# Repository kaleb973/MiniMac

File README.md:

# MiniMac
Presenting Mini Mac.   This is an external keypad to serve as functions that my current keyboard uses function keys for, like screenshot, which is (fn + u).   This project will serve as a huge productivity upgrade.

## Features
-128x32 OLED Display
-16 Keyswitches

## Note

I am also requesting a grant for a soldering iron (obviously with solder) for this project from Hack Club.

## Cad Model

I used heatset inserts and M3x16mm screws for the case. 

It has a simple Top and Bottom. The PCB sits in the middle.

This image displays the full model with the PCB inside.

Made in Fusion360.

## PCB

My PCB was made in KiCad

Schematic

PCB

## Firmware

This HackPad uses [QMK](https://qmk.fm/) firmware.

I intend to change the keys occasionally.

## BOM

Bill of Materials:

| Item | Description | Quantity |
| :--- | :--- | :--- |
| Cherry MX Switches | Keyswitches | 16 |
| DSA Keycaps | Keycaps | 16 |
| Heatset Inserts | Fasteners | 4 |
| M3x16mm Screws | Screws | 4 |
| 1N4148 Diodes | Through-Hole Diodes | 16 |
| 0.91-inch OLED Display | 128x32 Display | 1 |
| Seeed XIAO RP2040 | Microcontroller (unsoldered) | 1 |
| 3D Printed Case | 2 Parts (Top & Bottom) | 1 |

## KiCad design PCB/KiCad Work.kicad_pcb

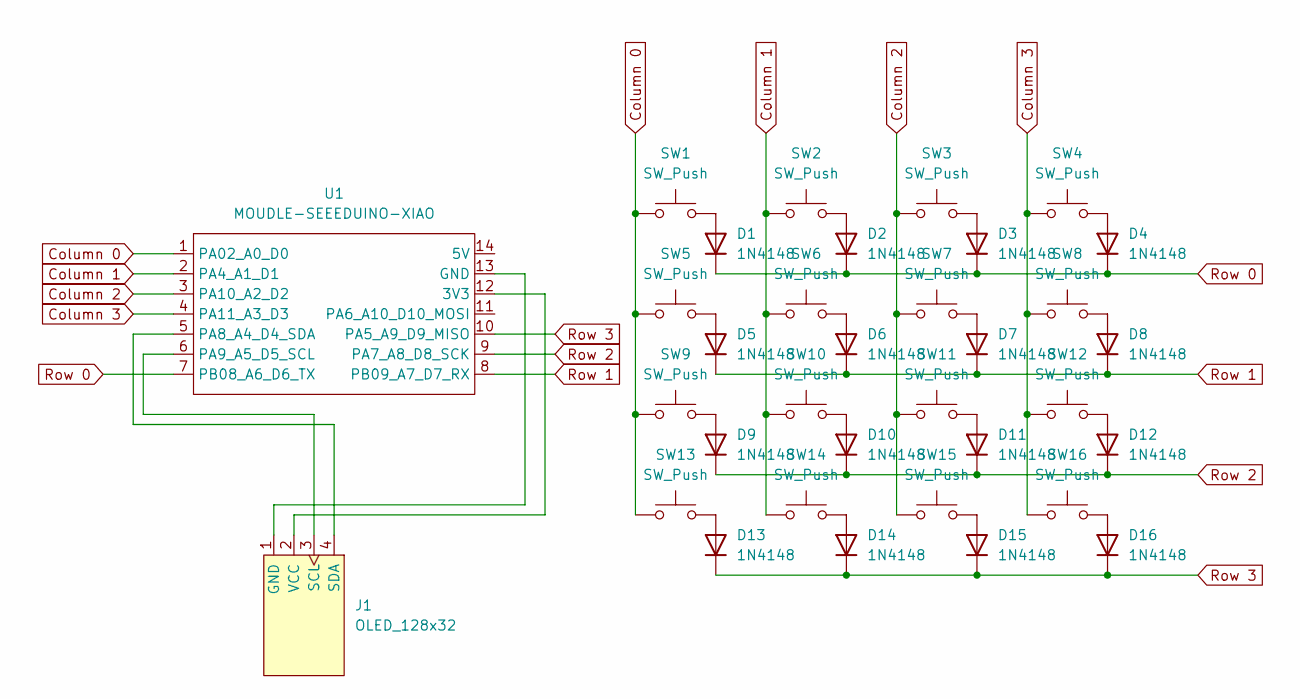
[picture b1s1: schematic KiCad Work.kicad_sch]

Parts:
D1, D2, D3, D4, D5, D6, D7, D8, D9, D10, D11, D12, D13, D14, D15, D16: 1N4148; D_DO-35_SOD27_P7.62mm_Horizontal
J1: OLED_128x32; SSD1306-0.91-OLED-4pin-128x32
SW1, SW2, SW3, SW4, SW5, SW6, SW7, SW8, SW9, SW10, SW11, SW12, SW13, SW14, SW15, SW16: SW_Push; SW_Cherry_MX_1.00u_PCB
U1: MOUDLE-SEEEDUINO-XIAO; XIAO-Generic-Hybrid-14P-2.54-21X17.8MM

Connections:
Column 0: SW1.1, SW5.1, SW9.1, SW13.1, U1.1 (PA02_A0_D0)
Column 1: SW2.1, SW6.1, SW10.1, SW14.1, U1.2 (PA4_A1_D1)
Column 2: SW3.1, SW7.1, SW11.1, SW15.1, U1.3 (PA10_A2_D2)
Column 3: SW4.1, SW8.1, SW12.1, SW16.1, U1.4 (PA11_A3_D3)
unnamed: D1.2 (A), SW1.2
unnamed: D2.2 (A), SW2.2
unnamed: D3.2 (A), SW3.2
unnamed: D4.2 (A), SW4.2
unnamed: D5.2 (A), SW5.2
unnamed: D6.2 (A), SW6.2
unnamed: D7.2 (A), SW7.2
unnamed: D8.2 (A), SW8.2
unnamed: D9.2 (A), SW9.2
unnamed: D10.2 (A), SW10.2
unnamed: D11.2 (A), SW11.2
unnamed: D12.2 (A), SW12.2
unnamed: D13.2 (A), SW13.2
unnamed: D14.2 (A), SW14.2
unnamed: D15.2 (A), SW15.2
unnamed: D16.2 (A), SW16.2
unnamed: J1.1 (GND), U1.13 (GND)
unnamed: J1.3 (SCL), U1.6 (PA9_A5_D5_SCL)
unnamed: J1.4 (SDA), U1.5 (PA8_A4_D4_SDA)
unnamed: J1.2 (VCC), U1.12 (3V3)
Row 0: D1.1 (K), D2.1 (K), D3.1 (K), D4.1 (K), U1.7 (PB08_A6_D6_TX)
Row 1: D5.1 (K), D6.1 (K), D7.1 (K), D8.1 (K), U1.8 (PB09_A7_D7_RX)
Row 2: D9.1 (K), D10.1 (K), D11.1 (K), D12.1 (K), U1.9 (PA7_A8_D8_SCK)
Row 3: D13.1 (K), D14.1 (K), D15.1 (K), D16.1 (K), U1.10 (PA5_A9_D9_MISO)

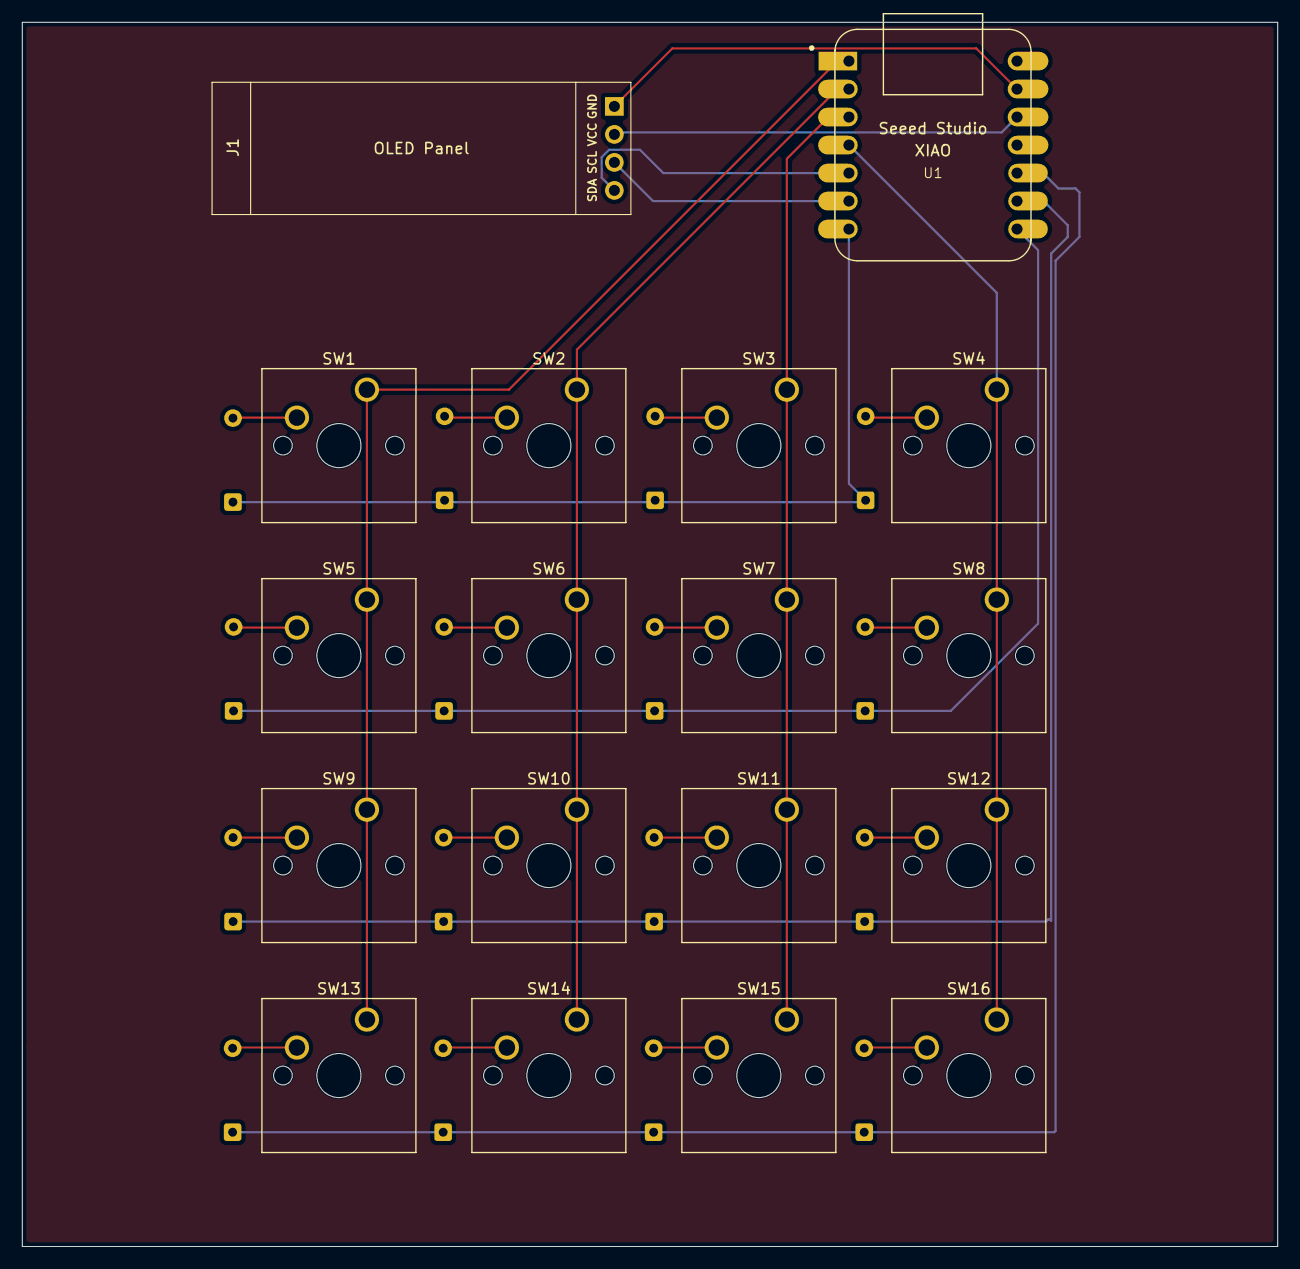
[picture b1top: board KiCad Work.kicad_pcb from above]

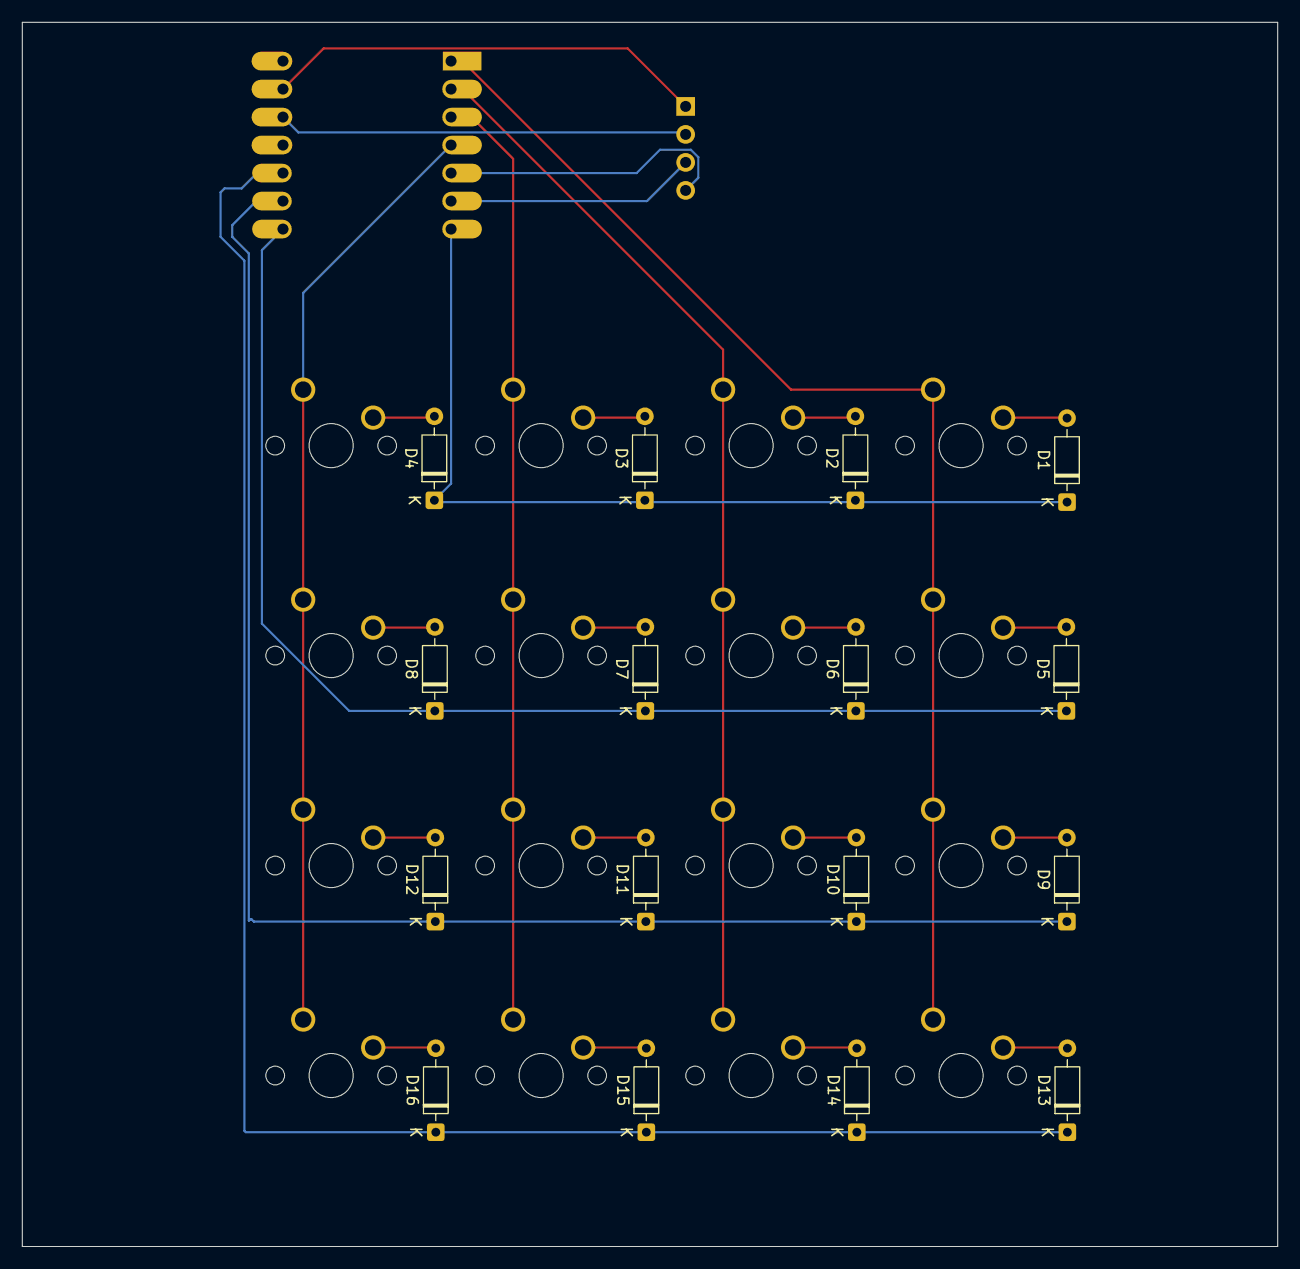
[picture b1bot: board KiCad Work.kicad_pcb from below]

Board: 2 copper layers, 113.9 x 111.1 mm, 34 parts (16 on the bottom side), 28 nets.
